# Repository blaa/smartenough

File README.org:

* Mono repository for all my smarthome needs.

In progress. Gathering and growing my smarthome tools.

** IO Controller MainBoard

- Cheap!
- Easy for DIY, even on a breadboard or soldered with wires.
- Uses available ready modules so there's not much to solder yourself.
- Assumes a distributed (using CAN), resiliant architecture.
- Based on STM32G431 WeAct module. Could be migrated to use other - eg. stm32f4.
- Has rudimentary (and optional) ESD protection using esda6v1s3.

[[hardware/board_v1.png]]
[[hardware/schematic_v1.png]]

*** Components:
- [https://github.com/WeActStudio/WeActStudio.STM32G431CoreBoard.git]
- CAN module, TJA1050 based.
- RS485 module, HW0519.
- Optional PCF8575 IO expanders (1-3)
- LM2596 stabilizer (30V+ -> 12V)
- MP1584 stabilizer (12V -> 5V)

** Greenfinger

Automatic plant watering using ESP8266 (or ESP32) using Micropython.
Integrates with HomeAssistant over MQTT:
- Reports status (humidity, operations).
- Can be controlled over MQTT (more water NOW).

It was 100% stable during a period of about a year. Plants died for unrelated
reasons. ;)

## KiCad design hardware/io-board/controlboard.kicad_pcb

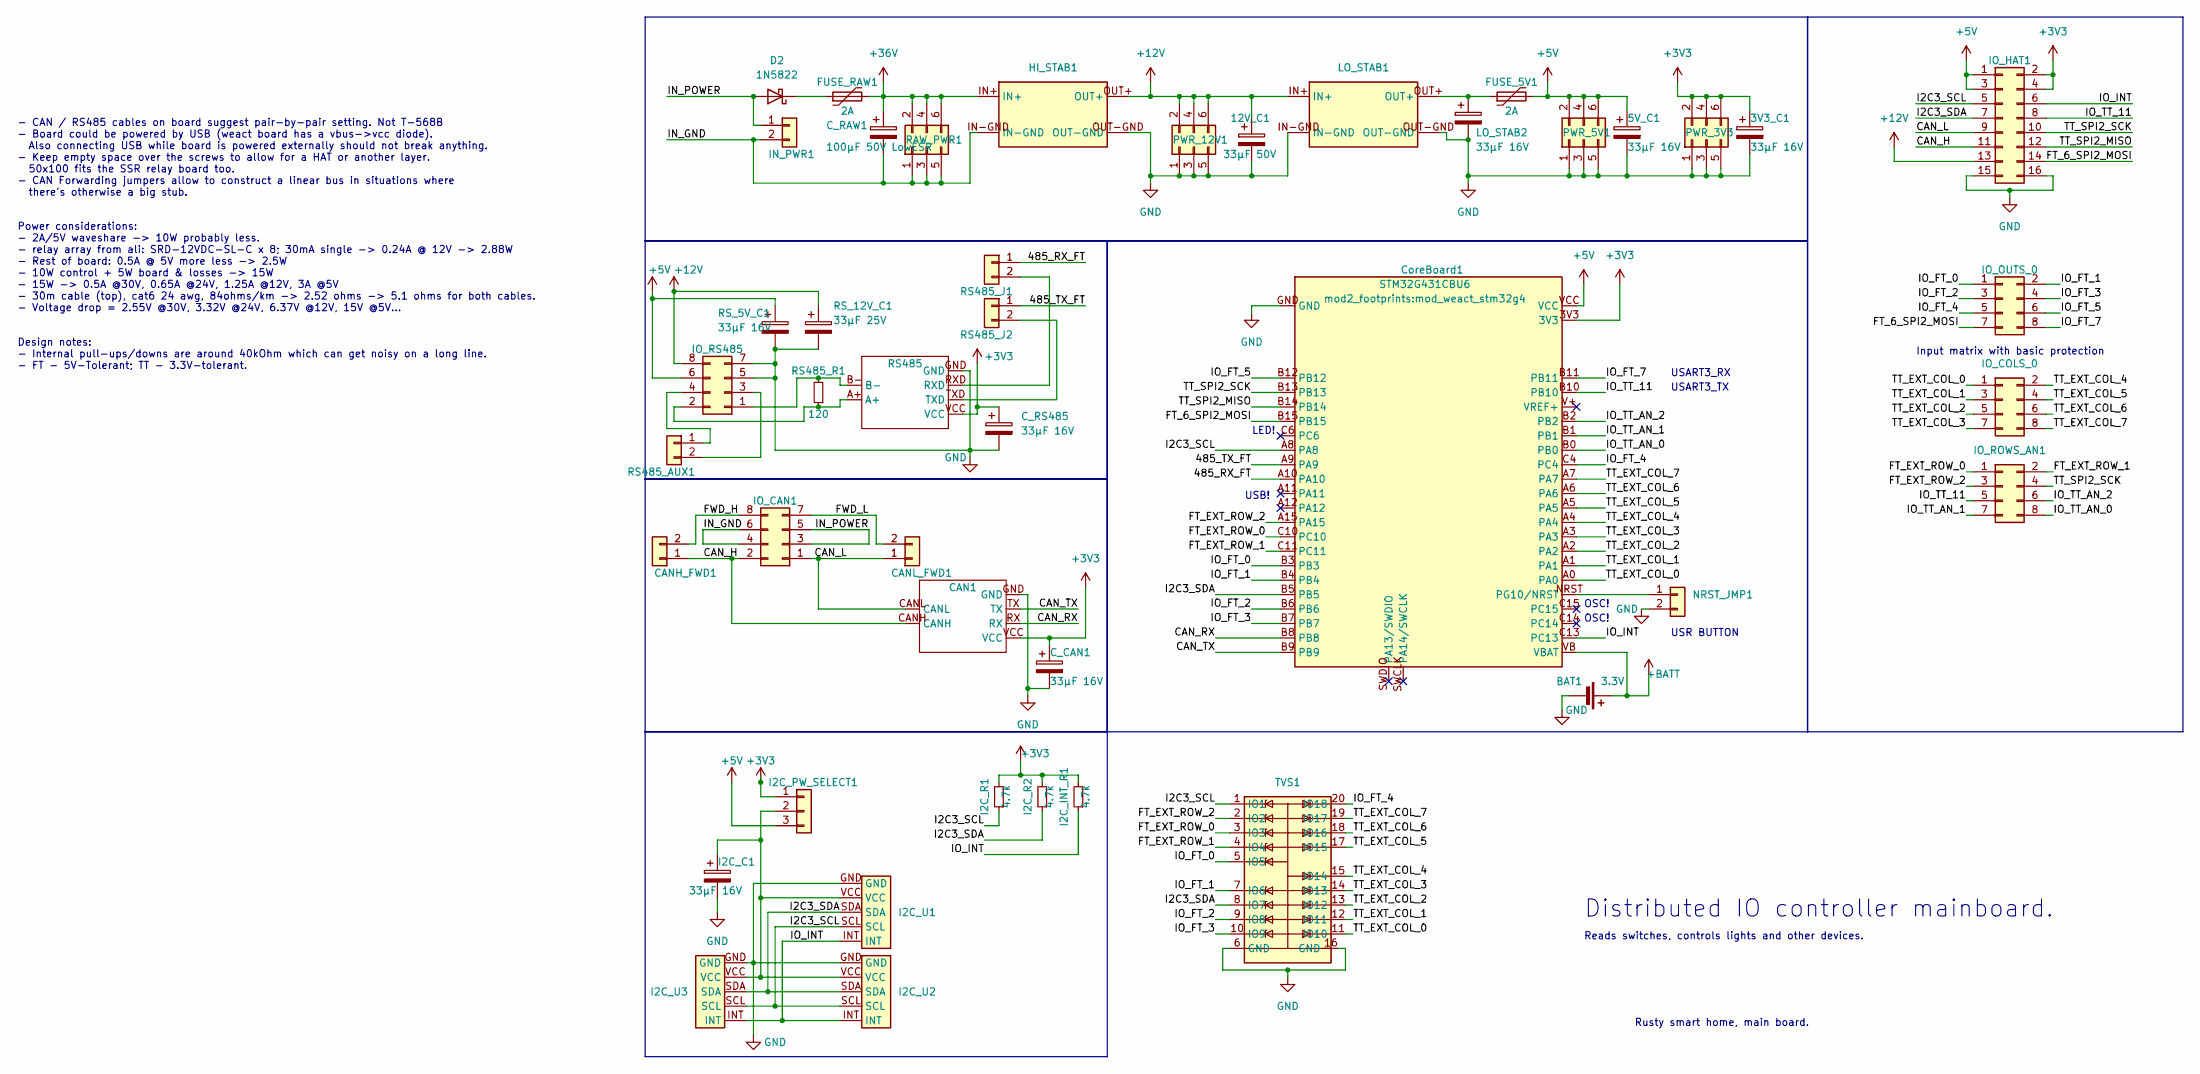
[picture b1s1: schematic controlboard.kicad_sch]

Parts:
3V3_C1, 5V_C1: 33µF 16V; C_Radial_D4.0mm_H7.0mm_P1.50mm
12V_C1: 33µF 50V; C_Radial_D5.0mm_H7.0mm_P2.00mm
BAT1: 3.3V; BatteryHolder_ComfortableElectronic_CH273-2450_1x2450
CAN1: mod_tja1050_can
CANH_FWD1: Conn_01x02; PinHeader_1x02_P2.54mm_Vertical
CANL_FWD1: Conn_01x02; PinHeader_1x02_P2.54mm_Vertical
C_CAN1: 33µF 16V; C_Radial_D4.0mm_H7.0mm_P1.50mm
C_RAW1: 100µF 50V LowESR; C_Radial_D10.0mm_H12.5mm_P5.00mm
C_RS485: 33µF 16V; C_Radial_D4.0mm_H7.0mm_P1.50mm
CoreBoard1: STM32G431CBU6; mod_weact_stm32g4
D2: 1N5822; D_DO-201AD_P15.24mm_Horizontal
FUSE_5V1: 2A; Fuse_BelFuse_0ZRE0016FF_L9.9mm_W3.8mm
FUSE_RAW1: 2A; Fuse_BelFuse_0ZRE0016FF_L9.9mm_W3.8mm
HI_STAB1: mod_LM2596
I2C_C1: 33µF 16V; C_Radial_D4.0mm_H7.0mm_P1.50mm
I2C_INT_R1, I2C_R1, I2C_R2: 4.7k; R_0805_2012Metric_Pad1.20x1.40mm_HandSolder
I2C_PW_SELECT1: Conn_01x03; PinHeader_1x03_P2.54mm_Vertical
I2C_U1, I2C_U2, I2C_U3: mod_pcf8575_16bit_vertical
IN_PWR1: Conn_01x02; PinHeader_1x02_P2.54mm_Vertical
IO_CAN1: Conn_02x04_Odd_Even; PinHeader_2x04_P2.54mm_Vertical
IO_COLS_0: Conn_02x04_Odd_Even; PinHeader_2x04_P2.54mm_Vertical
IO_HAT1: Conn_02x08_Odd_Even; PinHeader_2x08_P2.54mm_Vertical
IO_OUTS_0: Conn_02x04_Odd_Even; PinHeader_2x04_P2.54mm_Vertical
IO_ROWS_AN1: Conn_02x04_Odd_Even; PinHeader_2x04_P2.54mm_Vertical
IO_RS485: Conn_02x04_Odd_Even; PinHeader_2x04_P2.54mm_Vertical
LO_STAB1: mod_mp1584_stab
LO_STAB2: 33µF 16V; C_Radial_D5.0mm_H7.0mm_P2.00mm
NRST_JMP1: Conn_01x02; PinHeader_1x02_P2.54mm_Vertical
PWR_3V3, PWR_5V1, PWR_12V1: Conn_02x03_Odd_Even; PinHeader_2x03_P2.54mm_Vertical
RAW_PWR1: Conn_02x03_Odd_Even; PinHeader_2x03_P2.54mm_Vertical
RS485: mod_hw-0519-rs-485
RS485_AUX1, RS485_J1, RS485_J2: Conn_01x02; PinHeader_1x02_P2.54mm_Vertical
RS485_R1: 120; R_0805_2012Metric_Pad1.20x1.40mm_HandSolder
RS_5V_C1: 33µF 16V; C_Radial_D4.0mm_H7.0mm_P1.50mm
RS_12V_C1: 33µF 25V; C_Radial_D4.0mm_H7.0mm_P1.50mm
TVS1: SO-20_5.3x12.6mm_P1.27mm

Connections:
+3V3: 3V3_C1.1, CAN1.VCC, C_CAN1.1, C_RS485.1, CoreBoard1.3V3, I2C_INT_R1.2, I2C_PW_SELECT1.1, I2C_R1.2, I2C_R2.2, IO_HAT1.2, IO_HAT1.4, PWR_3V3.2, PWR_3V3.4, PWR_3V3.6, RS485.VCC
+5V: 5V_C1.1, CoreBoard1.VCC, FUSE_5V1.2, I2C_PW_SELECT1.3, IO_HAT1.1, IO_HAT1.3, IO_RS485.6, PWR_5V1.2, PWR_5V1.4, PWR_5V1.6, RS_5V_C1.1
+12V: 12V_C1.1, HI_STAB1.OUT+, IO_HAT1.13, IO_RS485.8, LO_STAB1.IN+, PWR_12V1.2, PWR_12V1.4, PWR_12V1.6, RS_12V_C1.1
+36V: C_RAW1.1, FUSE_RAW1.2, HI_STAB1.IN+, RAW_PWR1.2, RAW_PWR1.4, RAW_PWR1.6
+BATT: BAT1.1 (+), CoreBoard1.VB (VBAT)
/485_RX_FT: CoreBoard1.A10, RS485_J1.1
/485_TX_FT: CoreBoard1.A9, RS485_J2.1
/CAN_H: CAN1.CANH, CANH_FWD1.1, IO_CAN1.2, IO_HAT1.11
/CAN_L: CAN1.CANL, CANL_FWD1.1, IO_CAN1.1, IO_HAT1.9
/CAN_RX: CAN1.RX, CoreBoard1.B8
/CAN_TX: CAN1.TX, CoreBoard1.B9
/FT_6_SPI2_MOSI: CoreBoard1.B15, IO_HAT1.14, IO_OUTS_0.7
/FT_EXT_ROW_0: CoreBoard1.C10, IO_ROWS_AN1.1, TVS1.3 (IO3)
/FT_EXT_ROW_1: CoreBoard1.C11, IO_ROWS_AN1.2, TVS1.4 (IO4)
/FT_EXT_ROW_2: CoreBoard1.A15, IO_ROWS_AN1.3, TVS1.2 (IO2)
/I2C3_SCL: CoreBoard1.A8, I2C_R1.1, I2C_U1.SCL, I2C_U2.SCL, I2C_U3.SCL, IO_HAT1.5, TVS1.1 (IO1)
/I2C3_SDA: CoreBoard1.B5, I2C_R2.1, I2C_U1.SDA, I2C_U2.SDA, I2C_U3.SDA, IO_HAT1.7, TVS1.8 (IO7)
/IN_GND: C_RAW1.2, HI_STAB1.IN-GND, IN_PWR1.2, IO_CAN1.4, IO_CAN1.6, RAW_PWR1.1, RAW_PWR1.3, RAW_PWR1.5
/IN_POWER: D2.2 (A), IN_PWR1.1, IO_CAN1.3, IO_CAN1.5
/IO_FT_0: CoreBoard1.B3, IO_OUTS_0.1, TVS1.5 (IO5)
/IO_FT_1: CoreBoard1.B4, IO_OUTS_0.2, TVS1.7 (IO6)
/IO_FT_2: CoreBoard1.B6, IO_OUTS_0.3, TVS1.9 (IO8)
/IO_FT_3: CoreBoard1.B7, IO_OUTS_0.4, TVS1.10 (IO9)
/IO_FT_4: CoreBoard1.C4, IO_OUTS_0.5, TVS1.20 (IO18)
/IO_FT_5: CoreBoard1.B12, IO_OUTS_0.6
/IO_FT_7: CoreBoard1.B11, IO_OUTS_0.8
/IO_INT: CoreBoard1.C13, I2C_INT_R1.1, I2C_U1.INT, I2C_U2.INT, I2C_U3.INT, IO_HAT1.6
/IO_TT_11: CoreBoard1.B10, IO_HAT1.8, IO_ROWS_AN1.5
/IO_TT_AN_0: CoreBoard1.B0, IO_ROWS_AN1.8
/IO_TT_AN_1: CoreBoard1.B1, IO_ROWS_AN1.7
/IO_TT_AN_2: CoreBoard1.B2, IO_ROWS_AN1.6
/TT_EXT_COL_0: CoreBoard1.A0, IO_COLS_0.1, TVS1.11 (IO10)
/TT_EXT_COL_1: CoreBoard1.A1, IO_COLS_0.3, TVS1.12 (IO11)
/TT_EXT_COL_2: CoreBoard1.A2, IO_COLS_0.5, TVS1.13 (IO12)
/TT_EXT_COL_3: CoreBoard1.A3, IO_COLS_0.7, TVS1.14 (IO13)
/TT_EXT_COL_4: CoreBoard1.A4, IO_COLS_0.2, TVS1.15 (IO14)
/TT_EXT_COL_5: CoreBoard1.A5, IO_COLS_0.4, TVS1.17 (IO15)
/TT_EXT_COL_6: CoreBoard1.A6, IO_COLS_0.6, TVS1.18 (IO16)
/TT_EXT_COL_7: CoreBoard1.A7, IO_COLS_0.8, TVS1.19 (IO17)
/TT_SPI2_MISO: CoreBoard1.B14, IO_HAT1.12
/TT_SPI2_SCK: CoreBoard1.B13, IO_HAT1.10, IO_ROWS_AN1.4
GND: 3V3_C1.2, 5V_C1.2, 12V_C1.2, BAT1.2 (-), CAN1.GND, C_CAN1.2, C_RS485.2, CoreBoard1.GND, HI_STAB1.OUT-GND, I2C_C1.2, I2C_U1.GND, I2C_U2.GND, I2C_U3.GND, IO_HAT1.15, IO_HAT1.16, IO_RS485.5, IO_RS485.7, LO_STAB1.IN-GND, LO_STAB1.OUT-GND, LO_STAB2.2, NRST_JMP1.2, PWR_3V3.1, PWR_3V3.3, PWR_3V3.5, PWR_5V1.1, PWR_5V1.3, PWR_5V1.5, PWR_12V1.1, PWR_12V1.3, PWR_12V1.5, RS485.GND, RS_5V_C1.2, RS_12V_C1.2, TVS1.6 (GND), TVS1.16 (GND); also elsewhere on the board
unnamed: CANH_FWD1.2, IO_CAN1.8
unnamed: CANL_FWD1.2, IO_CAN1.7
unnamed: CoreBoard1.NRST (PG10/NRST), NRST_JMP1.1
unnamed: D2.1 (K), FUSE_RAW1.1
unnamed: FUSE_5V1.1, LO_STAB1.OUT+, LO_STAB2.1
unnamed: I2C_C1.1, I2C_PW_SELECT1.2, I2C_U1.VCC, I2C_U2.VCC, I2C_U3.VCC
unnamed: IO_RS485.1, RS485.B-, RS485_R1.2
unnamed: IO_RS485.2, RS485.A+, RS485_R1.1
unnamed: IO_RS485.3, RS485_AUX1.2
unnamed: IO_RS485.4, RS485_AUX1.1
unnamed: RS485.RXD, RS485_J1.2
unnamed: RS485.TXD, RS485_J2.2

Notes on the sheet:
USR BUTTON
Rusty smart home, main board.
LED!
- CAN / RS485 cables on board suggest pair-by-pair setting. Not T-568B - Board could be powered by USB (weact board has a vbus->vcc diode). Also connecting USB while board is powered externally should not break anything. - Keep empty space over the screws to allow for a HAT or another layer. 50x100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
Reads switches, controls lights and other devices.
USB!
Power considerations: - 2A/5V waveshare -> 10W probably less. - relay array from ali: SRD-12VDC-SL-C x 8; 30mA single -> 0.24A @ 12V -> 2.88W - Rest of board: 0.5A @ 5V more less -> 2.5W - 10W control + 5W board & losses -> 15W - 15W -> 0.5A @30V, 0.65A @24V, 1.25A @12V, 3A @5V - 30m cable (top), c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
OSC!
Distributed IO controller mainboard.
Design notes: - Internal pull-ups/downs are around 40kOhm which can get noisy on a long line. - FT - 5V-Tolerant; TT - 3.3V-tolerant.
Input matrix with basic protection
USART3_RX
USART3_TX

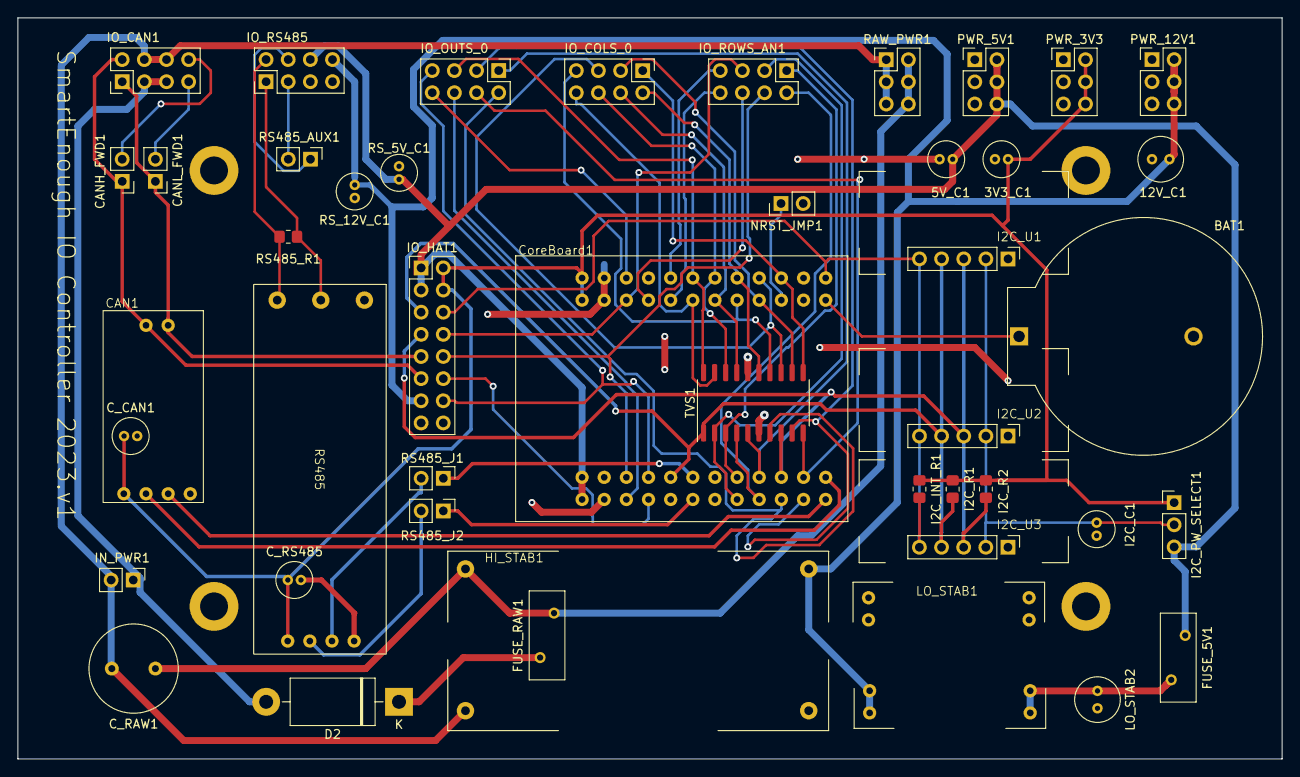
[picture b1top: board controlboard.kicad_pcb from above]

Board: 2 copper layers, 145.0 x 85.0 mm, 49 parts (0 on the bottom side), 54 nets.

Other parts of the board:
MHOLE_BL: MountingHole_3.2mm_M3_DIN965_Pad
MHOLE_RB: MountingHole_3.2mm_M3_DIN965_Pad
MHOLE_RT: MountingHole_3.2mm_M3_DIN965_Pad
MHOLE_TL: MountingHole_3.2mm_M3_DIN965_Pad

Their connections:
GND: MHOLE_BL.1, MHOLE_RB.1, MHOLE_RT.1, MHOLE_TL.1; also elsewhere on the board

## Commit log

2020-08-19 Initializing SmartEnough.
2020-08-21 Green finger, some iteration. Mostly own code here.
2020-08-21 Libraries for UMQTT and HA. Modified, but with outside sources.
2020-08-21 OLED display library
2020-08-25 Add MIT License. Most libraries are MIT anyway
2023-12-31 Schematic and board for the smarthome IO controller.
    Version 1. Probably has some problems.
2024-01-01 Hardware screenshots and README update.
